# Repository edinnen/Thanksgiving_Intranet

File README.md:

# Thanksgiving Intranet

Thanksgiving intranet server that does things.

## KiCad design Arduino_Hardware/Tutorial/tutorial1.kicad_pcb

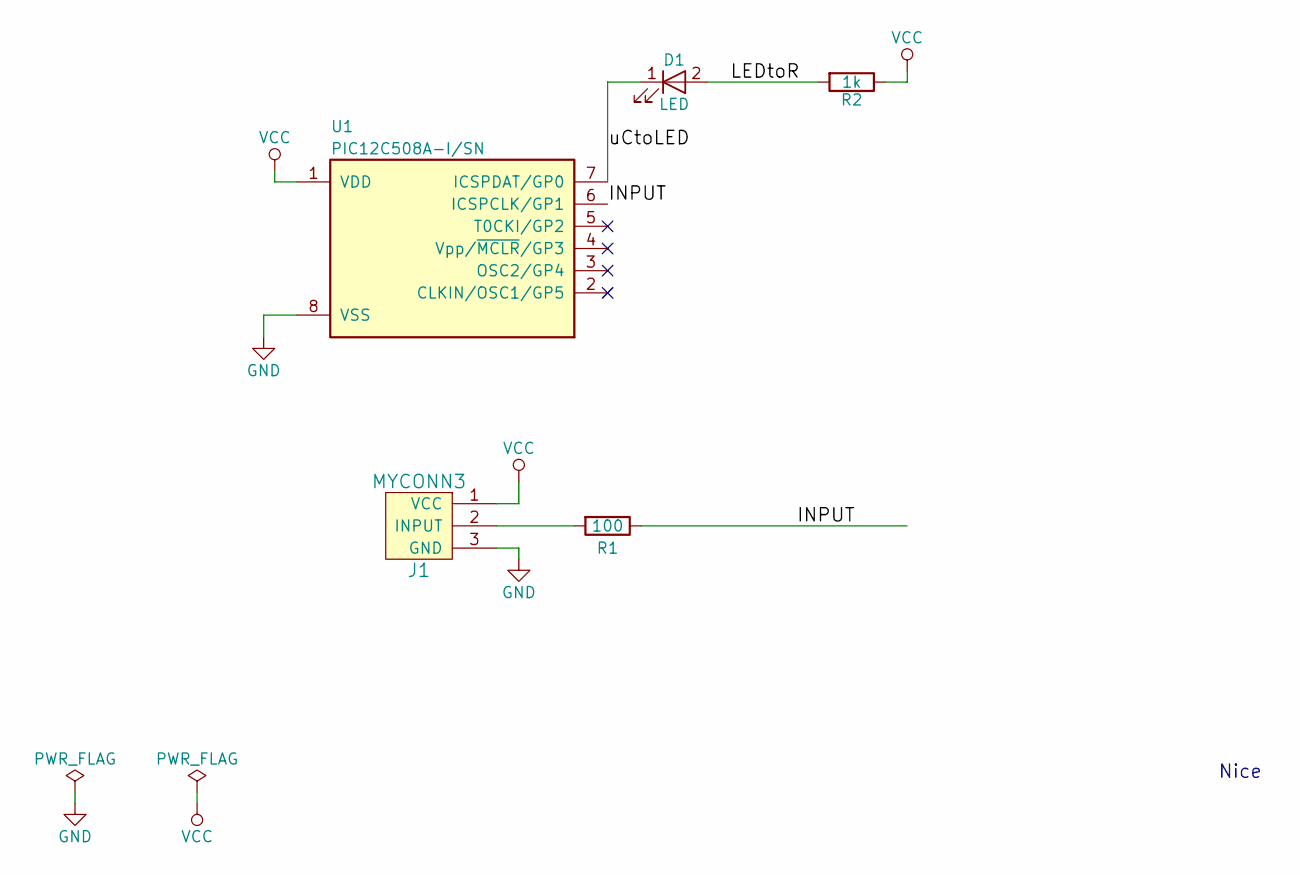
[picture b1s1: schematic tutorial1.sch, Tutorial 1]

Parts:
D1: LED; LED_D5.0mm
J1: MYCONN3; Banana_Jack_3Pin
R1: 100; R_2816_HandSoldering
R2: 1k; R_2816_HandSoldering
U1: PIC12C508A-I/SN; DIP-8_W7.62mm

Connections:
/INPUT: R1.1, U1.6 (ICSPCLK/GP1)
/LEDtoR: D1.2 (A), R2.2
/uCtoLED: D1.1 (K), U1.7 (ICSPDAT/GP0)
GND: J1.3 (GND), U1.8 (VSS)
unnamed: J1.2 (INPUT), R1.2
VCC: J1.1 (VCC), R2.1, U1.1 (VDD)

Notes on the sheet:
Nice

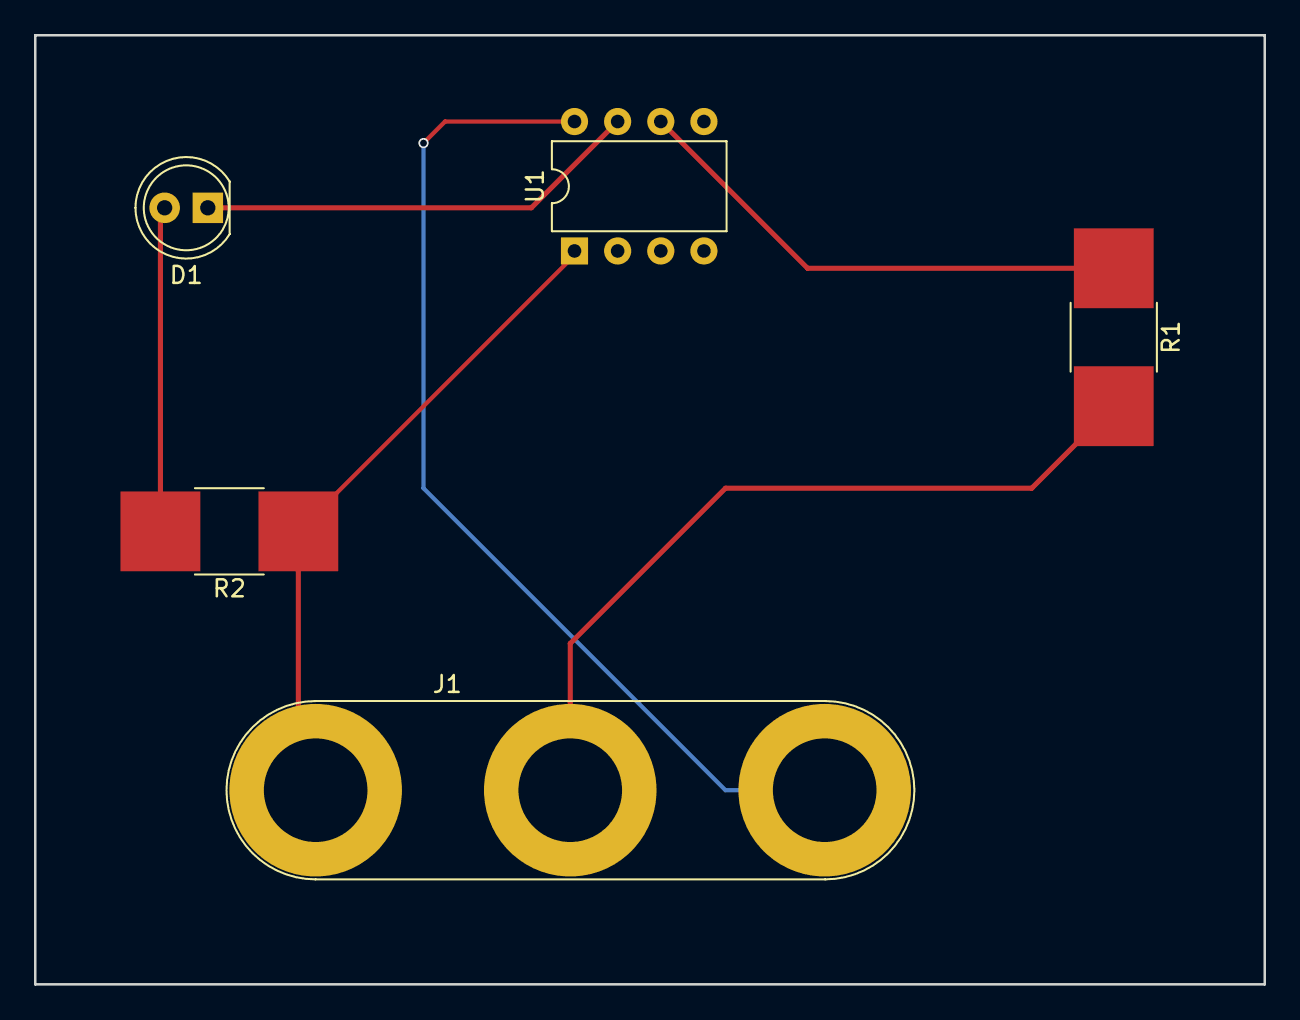
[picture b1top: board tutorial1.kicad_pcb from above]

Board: 2 copper layers, 72.4 x 55.9 mm, 5 parts (0 on the bottom side), 6 nets.

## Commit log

2017-09-23 Changed literally everything. Now using the following software stack: Golang for RESTful API, Docker for project building, React for frontend rendering, Postgres for database
2017-09-23 Updated nav. Added logbook functionality (still need to add date column in DB). Updated landing page. Added cleaning script and test log entry
2017-09-23 Update LICENSE
2017-09-24 Removed old site. Added date and delete confirm to logbook. Added TODO.md. Changed CDN CSS and Fonts to local copies. Added api/scripts/sample/sample.txt and api/scripts/powerData.py
2017-09-24 Added power stats page
2017-09-24 Updated TODO.md
2017-09-30 Added real time plot with random data
2017-09-30 Added system_monitor folder and initialized with files
2017-09-30 Started building the skeleton code for the arduino
2017-09-30 Started building the skeleton code for the arduino, also figuring out how to git-good
2017-10-01 Some actual functionality has been added. Still doesn't work though.
2017-10-01 test function added. It outputs stuff :)
2017-10-01 Test Functon: Analoge sensor readings, variable passing, string stuff
2017-10-02 More work on file naming and watchdog interupt. Added a vimrc
2017-10-03 Added RTC and SD card supprt. Dynamic file names and file header
2017-10-14 Writes data stream to serial and SD card. Files named correctly. Removed all floating point math for speed/efficiency
2017-10-15 Added two-direction serial control. Still buggy as dick though. A very buggy gross dick. Would not want that D
2017-10-15 Probably made it worse. SOOOO many stupid errors that make no logical sense. Trying to get data dumps to work but it somehow broke everything else. <3 C
2017-10-17 Added image uploading to Logbook. Images are encoded to Base64 with JavaScript and then sent to the Postgres database as a csv string. Added upload wait and completion notifications. Still need to im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
2017-11-24 Functioning live-updated power stats graph. Huzzah
2017-11-24 Updated plot styles; fixed width and responsivity
2017-12-12 Added document storage functionality with ownCloud. Build proccess is now much long and beautiful
2017-12-13 Updated OwnCloud navigation to link back to the main intranet page
2017-12-13 Added music playback functionality. Need to test with RPi audio device.
2017-12-13 Updated navbar with proper music link
2017-12-15 Added wiki
2018-02-24 Fixed file directory dump and changed filenames to be hexadecimal
2018-03-05 Updated voltage and current sensor calculations. Updated some comments.
2018-03-17 Fixed issue with kiwix download link
2018-03-20 Added new frontend and backend skeleton
2018-03-20 Removed botched nav
2018-03-25 Frontend now runs on RPi. Added AppBar route navigation and Drawer
2018-05-14 Started PCB Design, updated main sketch, created trouble shooting sketches too
2018-05-14 This time I totally did it. Added some folders
2018-07-16 Pretty much restared everything because I forgot how it worked... New working folder is 'TGC_monitor'
2018-07-17 It reads analog sensors, can tell the time, and is able to nap now!
2018-07-21 Has accurate time and outputs voltages and currents to sd card.
2018-07-22 Basic system flow works. Detects and reacts to Loads
2018-07-23 Got temperatures working. Pretty much functional now!
2018-07-23 Removed old web infrastructure and replaced with new framework. Added barebones test LED controls via pigpio Node library
2020-03-15 Got it working with the INA219 ICs! Way better!
2020-03-15 Got the time working better!
2020-03-16 Added energy and power monitoring. Also made times work better
2020-03-18 Started working on RPi part of the project. Files can be transfered. Poorly
2020-03-21 Got file transfers working to python
2020-03-22 Cleaned things up. Added more functionality
2020-03-22 hopefully removed the output files using gitignore
2020-03-22 removed the output files
2020-03-27 Split up the python code into two files
2020-03-27 Added piratebox stuff. Used for pi intranet
2020-03-27 Bump minimist from 1.2.0 to 1.2.2 in /Web_UI
    Bumps [minimist](https://github.com/substack/minimist) from 1.2.0 to 1.2.2.
    - [Release notes](https://github.com/substack/minimist/releases)
    - [Commits](https://github.com/substack/minimist/compare/1.2.0...1.2.2)
2020-03-27 Bump lodash from 4.17.10 to 4.17.13 in /Web_UI
    Bumps [lodash](https://github.com/lodash/lodash) from 4.17.10 to 4.17.13.
    - [Release notes](https://github.com/lodash/lodash/releases)
    - [Commits](https://github.com/lodash/lodash/compare/4.17.10...4.17.13)
2020-03-27 Bump axios from 0.18.0 to 0.18.1 in /Web_UI
    Bumps [axios](https://github.com/axios/axios) from 0.18.0 to 0.18.1.
    - [Release notes](https://github.com/axios/axios/releases)
    - [Changelog](https://github.com/axios/axios/blob/v0.18.1/CHANGELOG.md)
    - [Commits](https://github.com/axios/axios/compare/v0.18.0...v0.18.1)
2020-03-27 Bump react-dom from 16.4.1 to 16.4.2 in /Web_UI
    Bumps [react-dom](https://github.com/facebook/react/tree/HEAD/packages/react-dom) from 16.4.1 to 16.4.2.
    - [Release notes](https://github.com/facebook/react/releases)
    - [Changelog](https://github.com/facebook/react/blob/master/CHANGELOG.md)
    - [Commits](https://github.com/facebook/react/commits/v16.4.2/packages/react-dom)
2020-03-27 Bump extend from 3.0.1 to 3.0.2 in /Web_UI
    Bumps [extend](https://github.com/justmoon/node-extend) from 3.0.1 to 3.0.2.
    - [Release notes](https://github.com/justmoon/node-extend/releases)
    - [Changelog](https://github.com/justmoon/node-extend/blob/master/CHANGELOG.md)
    - [Commits](https://github.com/justmoon/node-extend/compare/v3.0.1...v3.0.2)
2020-03-27 Bump merge from 1.2.0 to 1.2.1 in /Web_UI
    Bumps [merge](https://github.com/yeikos/js.merge) from 1.2.0 to 1.2.1.
    - [Release notes](https://github.com/yeikos/js.merge/releases)
    - [Commits](https://github.com/yeikos/js.merge/compare/v1.2.0...v1.2.1)
2020-03-27 Bump mixin-deep from 1.3.1 to 1.3.2 in /Web_UI
    Bumps [mixin-deep](https://github.com/jonschlinkert/mixin-deep) from 1.3.1 to 1.3.2.
    - [Release notes](https://github.com/jonschlinkert/mixin-deep/releases)
    - [Commits](https://github.com/jonschlinkert/mixin-deep/compare/1.3.1...1.3.2)
2020-04-05 Bump minimist from 1.2.0 to 1.2.3 in /Web_UI
    Bumps [minimist](https://github.com/substack/minimist) from 1.2.0 to 1.2.3.
    - [Release notes](https://github.com/substack/minimist/releases)
    - [Commits](https://github.com/substack/minimist/compare/1.2.0...1.2.3)
2020-06-07 Cleaning up some folders
2020-06-15 Adds Go SSE server & analyzer. Adds app scaffolding
2020-06-15 Add SQLite database. Makes serial streaming more robust. Adds historical data download function
2020-06-16 Update the analyzer code
2020-06-16 Read in streamed file data
2020-06-16 Fixes TTY globbing
2020-06-16 Disable historical
2020-06-16 Add readline debug message
2020-09-19 messing with data processing
2020-10-05 Added a test program for the uC -> RPi communication
2020-10-08 Updates the Analyzer to handle historical data, streams, and time sync
2020-10-08 Adds sample frontend with Plotly
2020-10-08 Modifies Arduino code
2020-10-09 Removes old frontend
2020-10-10 Adds API for interfacing with frontend
2020-10-10 Removed old frontend
2020-10-27 Adds statistics module to analyzer. Various changes
2020-10-27 Adds survivorLibrary crawler
2020-10-27 Updates gitignore
2020-10-29 Adds anomalous data detection; SPA hosting; log to file
2020-10-31 Adds anomaly API endpoints
2020-10-31 Adds function/struct comments
2020-10-31 Adds CabinOS directory and .img shrink make function
2020-10-31 Adds another foreign key to anomalies_users
2020-11-02 Removes pirate box files
2020-11-03 Configured git LFS and added CabinOS.img
2020-11-10 Remove lfs
2020-11-10 Remove imgs
2020-12-23 Purging everything, we shall now rebuild!
2020-12-23 removed .swp files, testing ssh connection
2020-12-24 Working code ready to start first full hardware test
2020-12-26 Organized things nicer and made the timers more logical
2020-12-28 Tested and seems to be working well! Gonna bring this up to the Cabin
2020-12-29 Playing around with some more timers
2021-01-02 This is what was installed at the cabin, still has some quirks...
2021-01-31 fixed how power is logged and recorded. Sorry, changed the serial output again...
2021-07-25 asbuilt at TGC
2021-07-25 Corrected the INA219 addresses and fixed a bug in the data handling (loadA was battA in one spot)
2021-07-25 Got the debug load monitor working correctly. Verified/adjusted settings of the INA219s. Pretty sure the logging should be working
2021-07-25 Updated the python scrips so they can download and display the data properly
2021-08-08 As-built at TGC. Actually works now which is cool
2021-08-08 fixing graph
2021-10-23 As built at Cabin
2021-10-23 updating TGC file processing
2021-10-23 Update data format parsing
2021-10-23 Change log calls
2021-10-23 Change stream stop command & serial init
2021-10-23 Change historical filename parsing
2021-10-23 Bring in line with Arduino changes
2021-10-24 Optimizing code for pi
2021-10-24 Add debug flag
2021-10-24 Add toFile arg
2021-10-24 Add database and logfile path flags
2021-10-24 Disable statistics engine
2021-10-24 Don't download recieved historical files
2021-10-24 Add where to select query
2021-10-24 Loop for file before go func declaration
2021-10-25 Configure Github Actions
2021-10-25 Update CI
2021-10-25 Added arduino libraries. Updated code for test uC
2021-10-25 Added uC libraries
2021-10-25 Enable CI arduino complition and sketch upload
2021-10-25 Git pull before compile
2021-10-25 Remove reference to frontend
2021-10-25 Remove gitmodules
2021-10-25 Add frontend code
2021-10-25 Print historical file insert error
2021-10-25 Build and upload frontend via CI
2021-10-25 Removed submodule
2021-10-25 Added frontend
2021-10-25 Updated CI to be conditional
2021-10-25 Change change detection job name
2021-10-25 Remove cyclic need
2021-10-25 Changed toggle stream to ON OFF, 4 and 8 for RPi
2021-10-25 Remove unused frontend pages
2021-10-25 Fix CI
2021-10-25 Add logbook page
2021-10-25 Adds babel-eslint
2021-10-25 Add a rudimentary logbook
2021-10-25 Add new data values
2021-10-25 Preload fonts
2021-10-25 Update README and Github Action
2021-10-25 Only halt/start system if changes made to core systems
2021-10-25 Update and re-enable anomaly tracking
2021-10-25 Fix invalid operation
2021-10-25 Remove submodule reference to Time library
2021-10-25 Fix workflow system start
2021-10-25 Properly break historical read loop on EOF
2021-10-25 Disable sqlite3 shared cache
2021-10-27 Added jupyter notebook data processing
2021-10-28 Remove cache argument for db connection
2022-12-28 More jupyter fun added
